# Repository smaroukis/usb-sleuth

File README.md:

See [this README](/README-downloading-firmware.md) for usage of the STM32CubeIDE to flash firmware on the device. 

## Overview

The device tests for continuity and internal resistors within various USB Cables and exposes some pins for multimeter testing. The project is a hardware fork of [aroerina/LimePulse](https://github.com/aroerina/LimePulse_USB_cable_checker/) that I decided to reverse engineer and write the firmware for.

A STM32C031K6T microcontroller is used for testing connection and orientation, powered by a CR2032 battery. Code is given using STM32 HAL libraries and the device can being programmed over SWD. 

KiCad and gerber files are provided for the board layout, as well as the library footprints for non-standard parts ordered from JLCPCB/LCSC. 
See the [BOM](/production/38-04-usb-tester_2023-12-18_rev1/bom.csv).

This USB cable tester has the "B" side on the right, and the "A" side on the left. Receptacles are given for the following:
- Type-C (both sides) 
- Type-C to A 
- Type-C to micro B (2.0)
- Type-C to mini B 

The device has some benefits over a simple continuity tester
- displays the as-plugged orientation of the 4 different possibilities of the USB-C to C cable
- detects pullup and pulldown resistors on the CC lines as required by the USB standard for legacy cables 
- identifies active cable with E marker (via the pulldown resistor present on VCONN)
- doesn't apply a +V to the Ground line/pin, instead it uses a MCU to test the presence of a connected ground wire
- exposes various pins to test cable and internal resistors manually with a DMM

## Example Tests

#### USB C-C Active Cable

> Note in this test only one of the USB 2.0 Data pair LEDs will light up depending on the cable orientation, showing that the two pairs are not connected inside the cable (the pairs are also not connected on the PCB). The user must flip the orientation to test both data pairs. 
#### DMM Test of Internal Resistor

Testing the value of the pulldown resistor on an active cable by measuring between `B_CC2` and `B_GND` (should be between 800-1.2K Ohms).

#### OTG Test

## General PCB Layout

Layout
- Various B side pins are biased to VBUS through pullup resistors. A side pins are either connected to ground through an LED, thus lighting up if the corresponding wire is continuous, or the pins are connected into the MCU for inputs. These pins that the MCU tests for are as follows:
- Ground (note all four GND pins are tied together)
- VBUS (note all four VBUS pins are tied together)
- CC1 to test for CC line and orientation
- CC2 to test for VCONN line and pull down resistor for active cables, as well as a flipped CC cable

> Note: Both A-side and B-side CC1 and CC2 pins are tapped off into corresponding control inputs to the MCU through a resistor, allowing for pulling the control pins high or low to sense the result on the opposite side.

Simplified layout of testing CC1 pin.

## Programming and Reset

Programming is done via the Serial Wire Debug headers (labeled `DEBUG`) via an STLink debugger probe. 

The device can also be reset by shorting out the `nRESET` line to `GND` (pins 1 and 2 on the header).

> [!CAUTION]
> In the case where the debugger is providing power to the target, make sure the `POWER` switch is `OFF`.

> [!NOTE]
> For the `SWD` pins we need pullup or pulldown resistors on `SWDIO` and `SDCLK` respectively. These are provided internally by the STM32 MCU, but if there is an issue with the debugger try adding an external weak pulllup and pulldown (10K-100K).

# Description of Operation

## Sensing VBUS and GND 

> [!NOTE]
> `VBUS`: Pulled up on B-side to VDD via 2K, pulled down to ground at A-side MCU input sense pin via 10K. Sense pin reads high if VBUS line is continuous through the cable.
> `GND`: B-side receptacle ground pin connected to board ground, A-side receptacle pin is direct to input sense pin.

All VBUS pins are tied together and tested via a pulldown resistor on the MCU (similarly for GND pins).

Most B-side receptacle pins are pulled up to supply/VDD through resistors with exception for CC pins and Ground. B-side ground is connected to board ground through a DIP switch for isolation from the MCU ground if needed.

A-side receptacle pins are connected to the MCU input for sensing.

`A_VBUS`/`A_GND` and connected to `VBUS_SENSE`/`GND_SENSE` inputs to the MCU through DIP switches for isolation from the MCU during DMM testing.

`VBUS_SENSE` pin is an input to the MCU with a pull down resistor forming a voltage divider with the 2K VDD pulllup resistor. If the `VBUS` line is discontinuous, the pin reads `LOW`. If `VBUS` is continuous then the pin reads `VCC`x10/12, or digital `HIGH`. 

Indicator LEDs are driven by the MCU outputs `GND_LED` and `VBUS_LED`.

# MCU Testing Logic

### Orientation of CC Pin

Here is the type-C receptacle pinout 

> Source: "USB 2.0 Type-C Plug Pin-Out" https://ww1.microchip.com/downloads/en/appnotes/00001953a.pdf

Possible orientations of USB-C Plug. 

> Note Ra is for the active pulldown emarker, but don't take this "straight through" configuration literally as there are diodes preventing shorting of the pins.

Simplified PCB layout:

We can determine that a C-C type cable is connected by pulling both A_CC1 and A_CC2 HIGH and CCx_CTRL pins LOW, then looking for one of the B_CCx pins coming HIGH.

### MCU Testing of Ra on Emarker (Active) Cables

The pulldown (Ra, for "active") is nominally 800-1.2K. Connection is as follows:

We simply configure the `A_CC2` and `B_CC2` pins as `INPUT_PULLUP`s and test if these lines (the `VCONN` line) are pulled low (normally it is open), since the pulldown Ra is strong at ~1K.

## MCU Testing of Rp on Type-A to Type-C Cable

> [!NOTE]
> It is programmed to work for both USB-C plug orientations

Setup
1. `VBUS` is connected to `VCC` through a 2K resistor (ignored for the calculations below)
2. Write `CC1_CTRL` and `CC2_CTRL` → `LOW` (pulls `B_CCx` pin toward ground through 10K R)
3. Perform analog read of `B_CC1_sense` and `B_CC2_SENSE`
4. If the analog read is above a threshold, `RP_THRESH`, to account for ground noise, then the 56K Rp pullup exists. 

> [!TIP]
> An analog read is required since the internal Rp is weak enough such that it doesn't pull it all the way up to the digital `HIGH` threshold

## MCU Testing of Rd on Type-B to Type-C Cable

> Note this works for both CC configurations

1. Set `A_CC1` as `INPUT_PULLUP` (~50K internal pullup)
2. Read `A_CC1`, if pulled `LOW`, then it means that `Rp` is present (Rd = 5K which is much stronger than the 50K internal pullup)

## Power Isolation For Testing

Isolation switches are provided to isolate the DMM from the MCU as it injects a test current to measure resistance, and also to allow us to measure the resistance of the cable itself (e.g. VBUS to GND). 

> Note during testing it was found that even with the switches closed the DMM measurements weren't affected.  

In the schematic these are modeled as a multi-unit DIP switch:
- `SW2A`: Separates `VCC` from `VBUS`
- `SW2B`: Separates `B_GND` from `GND`
- `SW2C`: Separates `A_GND` from `A_GND_SENSE` (input to MCU)
- `SW2D`: Separates `A_VBUS` from `A_VBUS_SENSE` (input to MCU)

# DMM Testing

## DMM Testing of  Rp on CC line

> [!Caution]
> Verify the following:
> 1. USB cable is in the normal CC Orientation of `STD>STD` before proceeding (or note the configuration to choose the correct pad to test)
> 2. All DIP switches are in the OFF position
> 3. Power switch is in the OFF position

For the Type-A to C cable the USB standard specifies at 56K pullup resistor between `VBUS` and `CC` (since the A side is the host, CC pin needs to be pulled up for the B-side/peripheral to recognize A side as host). 

We can test the exact value of this resistor by using a DMM between `B_VBUS` and `B_CC1` testing pads.

## DMM Testing of Rd

> [!Caution]
> Verify the following:
> 1. USB cable is in the normal CC Orientation of `STD>STD` before proceeding (or note the configuration to choose the correct pad to test)
> 2. All DIP switches are in the OFF position
> 3. Power switch is in the OFF position

For the Type-B to C cable the USB standard specifies at 5K6 pulldown resistor between `CC` and `GND` (since the B side is the peripheral, CC pin needs to be pulled down for the A-side/host to recognize B side as peripheral). 

We can test the exact value of this resistor by using a DMM between 
`A_GND` and `A_CC1` 

## DMM Testing of Ra

1. With device ON, make sure the CC orientation is `STD>STD`
2. Switch isolation switches to OFF
3. Switch power OFF
4. Place a DMM between `B_CC2` and `B_GND` since the Ra will be on the VCONN line.

# Shields and ID Pin

### Shields 
Shields are connected together and exposed to a through hole testing terminal. For this we can test with a multimeter. 

Note the shield and ground are connected inside the receptacle.

### ID (On The Go / OTG)

The OTG specification allows a USB device normally acting as a peripheral, to now act as a host (example use case: a tablet normally a peripheral, acting as a host can read from removable media on a flash drive)

For the OTG cable the A-plug side ties its ID pin to ground, and the B-plug side leaves it floating.  

Since the ID pin is supposed to be tied to its ground pin within the plug, we just connect an LED between VDD → ID pin (=Ground pin) to test the connection.

> The ID pin is also brought out on an exposed pad.

# FAQ

Only one set of the D+ and D- pins light up.
- The D1+/- and D2+/- pins are not connected together to allows the user to test both sets of pins independently (but requires the user to flip the USB-C side)

OTG Cable test doesn't work? 
- Make sure the test setup is as shown in the examples

> If the OTG cable has two male plugs, the data lines are not connected between the male ends, only from female → male 1 and female → male 2. The proper way to test will require the OTG adapter plus a normal USB cable. 

With one end plugged in, when I touch the other cable plug to the receptacle the GND (and sometimes Rd) LEDs light up.
- This happens because the tester first checks for VBUS=+Vsupply, and next checks for Ground=0V. If GND=0V it waits 300ms for the plug to "seat" before running through the other tests. But since the receptacle chassis and plug sheath are connected to GND, if you touch the plug to the receptacle it will read GND as 0V and proceed with the other tests. In the USB C<>B case, the Rd test will run if the CC pins aren't connected through on both sides, so it will also test once this contact is made.

# Notable Documentation

The USB-C Type Spec provides the Rp and Rd requirements for legacy cables.

For example, Type-C to 2.0 Type A:

USB Type-C Spec R2.3 - October 2023.pdf
> tl;dr any legacy cable assembly that **sources** power to a Type C connector must use the default 56K pullup (note this is for both 3.1 and 2.0 versions, since the power negotiation didn't come along until later)

Note the A5 CC pin and the B5 VCONN pin are **not** connected internally. This means it is up to the hardware developer to implement orientation detection on the C-receptacle side. 

And here is for the Type-C to 2.0 Micro-B:
 ^dzdzs5

# Improvements
- USB C<> Micro/Mini B D+/D- LED pair is dependent on C side orientation - make it more user friendly by only lighting up the bottom 2.0 row
- Low power

# Attributions
**Icons**
- Fedora Hat by Sanjib Biswas from [vecteezy](https://www.vecteezy.com/png/24758745-fedora-hat-transparent-background) -  <a href="https://www.vecteezy.com/free-png/silhouette">Silhouette PNGs by Vecteezy</a>
- tip by Hothouse Design from <a href="https://thenounproject.com/browse/icons/term/tip/" target="_blank" title="tip Icons">Noun Project</a> (CC BY 3.0)
- Warning by Deylotus Creative Design from <a href="https://thenounproject.com/browse/icons/term/warning/" target="_blank" title="Warning Icons">Noun Project</a> (CC BY 3.0)

**Inspired By**
- https://github.com/petl/USB-C-cable-tester-C2C-caberQU
- https://github.com/alvarop/usb_c_cable_tester
- https://github.com/aroerina/LimePulse_USB_cable_checker/ - original inspiration for the design and functionality from its professional quality layout

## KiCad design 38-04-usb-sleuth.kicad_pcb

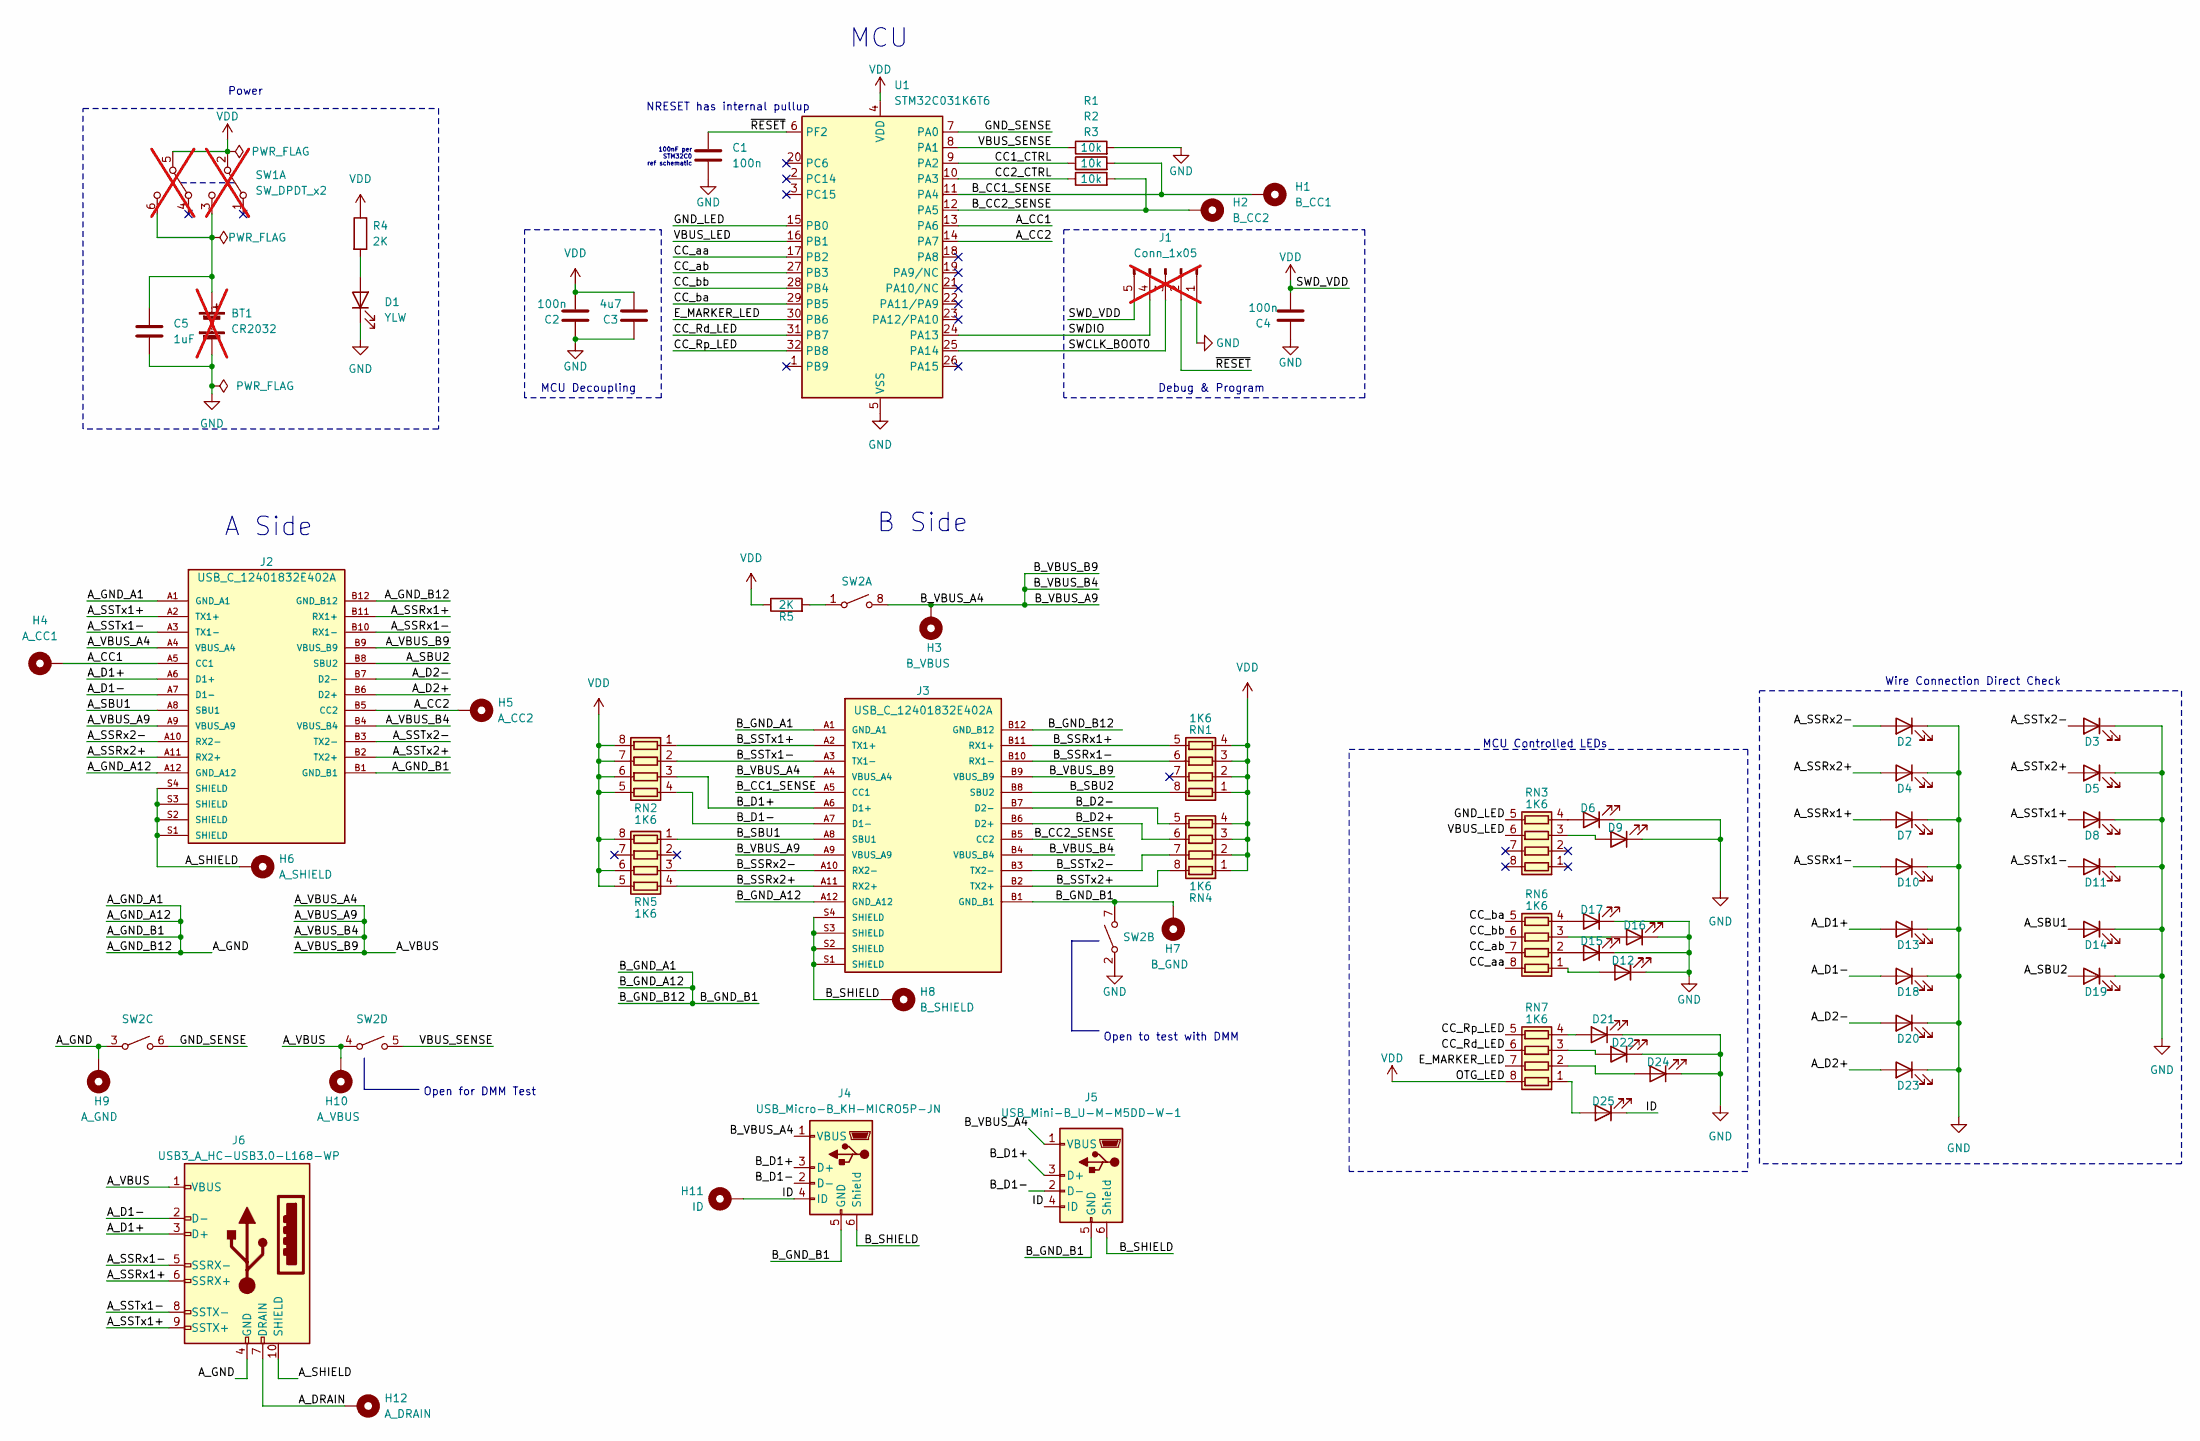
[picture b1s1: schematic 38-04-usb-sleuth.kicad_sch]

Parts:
BT1: CR2032; BatteryHolder_Keystone_103_1x20mm; LCSC Part # DNP; not fitted
C1, C2, C4: 100n; C_0402_1005Metric; LCSC Part # C1525
C3: 4u7; C_0805_2012Metric_Pad1.18x1.45mm_HandSolder; LCSC Part # C1779
C5: 1uF; C_0805_2012Metric_Pad1.18x1.45mm_HandSolder; LCSC Part # C28323
D1, D2, D3, D4, D5, D6, D7, D8, D9, D10, D11, D12, D13, D14, D15, D16, D17, D18, D19, D20, D21, D22, D23, D24, D25: YLW; LED_0805_2012Metric; LCSC Part # C2296
H1: B_CC1; Connector_Pad_Edge_Oval_5mm_Extended; LCSC Part # DNP
H2: B_CC2; Connector_Pad_Edge_Oval_5mm_Extended; LCSC Part # DNP
H3: B_VBUS; Connector_Pad_Edge_Oval_5mm_Extended; LCSC Part # DNP
H4: A_CC1; Connector_Pad_Edge_Oval_5mm_Extended; LCSC Part # DNP
H5: A_CC2; Connector_Pad_Edge_Oval_5mm_Extended; LCSC Part # DNP
H6: A_SHIELD; TestPoint_THTPad_D1.5mm_Drill0.7mm; LCSC Part # DNP
H7: B_GND; Connector_Pad_Edge_Oval_5mm_Extended; LCSC Part # DNP
H8: B_SHIELD; TestPoint_THTPad_D1.5mm_Drill0.7mm; LCSC Part # DNP
H9: A_GND; Connector_Pad_Edge_Oval_5mm_Extended; LCSC Part # DNP
H10: A_VBUS; Connector_Pad_Edge_Oval_5mm_Extended; LCSC Part # DNP
H11: ID; TestPoint_THTPad_D1.5mm_Drill0.7mm; LCSC Part # DNP
H12: A_DRAIN; TestPoint_THTPad_D1.5mm_Drill0.7mm; LCSC Part # DNP
J1: Conn_1x05; PinSocket_1x05_P2.54mm_Vertical; LCSC Part # DNP; not fitted
J2, J3: USB_C_12401832E402A; USB_C_Receptacle_Amphenol_12401832E402A; PARTREV X2; DigiKey_Part_Number 12401832E402ATR-ND
J4: USB_Micro-B_KH-MICRO5P-JN; USB_Micro-B_Kinghelm-KH-MICRO5P-JN; LCSC Part # C962222
J5: USB_Mini-B_U-M-M5DD-W-1; USB_Mini-B_Korean-Hroparts_U-M-M5DD-W-1_SMD-5-4MP; LCSC Part # C145778
J6: USB3_A_HC-USB3.0-L168-WP; USB3_A_Hong-Cheng_HC-USB3.0-L168-WP_THT-9-2MP_P2.0mm; LCSC Part # C7501850
R1, R2, R3: 10k; R_0805_2012Metric_Pad1.20x1.40mm_HandSolder; LCSC Part # C17414
R4, R5: 2K; R_0805_2012Metric_Pad1.20x1.40mm_HandSolder; LCSC Part # C17604
RN1, RN2, RN3, RN4, RN5, RN6, RN7: 1K6; R_Array_Concave_4x0402; LCSC Part # C728711
SW1: SW_DPDT_x2; SW_E-Switch_EG1271_SPDT; LCSC Part # DNP; not fitted
SW2: ZX-1.27BM-4PSMD; SW-DIP-4P_P1.27mm_SMD-2x4; LCSC Part # C5160896
U1: STM32C031K6T6; LQFP-32_7x7mm_P0.8mm; LCSC Part # C5456169

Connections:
/A_CC1: H4.1, J2.A5 (CC1), U1.13 (PA6)
/A_CC2: H5.1, J2.B5 (CC2), U1.14 (PA7)
/A_D1+: D13.2 (A), J2.A6 (D1+), J6.3 (D+)
/A_D1-: D18.2 (A), J2.A7 (D1-), J6.2 (D-)
/A_D2+: D23.2 (A), J2.B6 (D2+)
/A_D2-: D20.2 (A), J2.B7 (D2-)
/A_DRAIN: H12.1, J6.7 (DRAIN)
/A_GND: H9.1, J2.A1 (GND_A1), J2.A12 (GND_A12), J2.B1 (GND_B1), J2.B12 (GND_B12), J6.4 (GND), SW2.3
/A_GND_SENS: SW2.6, U1.7 (PA0)
/A_SBU1: D14.2 (A), J2.A8 (SBU1)
/A_SBU2: D19.2 (A), J2.B8 (SBU2)
/A_SHIELD: H6.1, J2.S1 (SHIELD), J2.S2 (SHIELD), J2.S3 (SHIELD), J2.S4 (SHIELD), J6.10 (SHIELD)
/A_SSRx1+: D7.2 (A), J2.B11 (RX1+), J6.6 (SSRX+)
/A_SSRx1-: D10.2 (A), J2.B10 (RX1-), J6.5 (SSRX-)
/A_SSRx2+: D4.2 (A), J2.A11 (RX2+)
/A_SSRx2-: D2.2 (A), J2.A10 (RX2-)
/A_SSTx1+: D8.2 (A), J2.A2 (TX1+), J6.9 (SSTX+)
/A_SSTx1-: D11.2 (A), J2.A3 (TX1-), J6.8 (SSTX-)
/A_SSTx2+: D5.2 (A), J2.B2 (TX2+)
/A_SSTx2-: D3.2 (A), J2.B3 (TX2-)
/A_VBUS: H10.1, J2.A4 (VBUS_A4), J2.A9 (VBUS_A9), J2.B4 (VBUS_B4), J2.B9 (VBUS_B9), J6.1 (VBUS), SW2.4
/A_VBUS_SENS: R1.1, SW2.5, U1.8 (PA1)
/B_CC1_SENS: H1.1, J3.A5 (CC1), R2.2, U1.11 (PA4)
/B_CC2_SENS: H2.1, J3.B5 (CC2), R3.2, U1.12 (PA5)
/B_D1+: J3.A6 (D1+), J4.3 (D+), J5.3 (D+), RN2.3 (R3.1)
/B_D1-: J3.A7 (D1-), J4.2 (D-), J5.2 (D-), RN2.4 (R4.1)
/B_D2+: J3.B6 (D2+), RN4.6 (R3.2)
/B_D2-: J3.B7 (D2-), RN4.5 (R4.2)
/B_GND_A1: H7.1, J3.A1 (GND_A1), J3.A12 (GND_A12), J3.B1 (GND_B1), J3.B12 (GND_B12), J4.5 (GND), J5.5 (GND), SW2.7
/B_SBU1: J3.A8 (SBU1), RN5.1 (R1.1)
/B_SBU2: J3.B8 (SBU2), RN1.8 (R1.2)
/B_SHIELD: H8.1, J3.S1 (SHIELD), J3.S2 (SHIELD), J3.S3 (SHIELD), J3.S4 (SHIELD), J4.6 (Shield), J5.6 (Shield)
/B_SSRx1+: J3.B11 (RX1+), RN1.5 (R4.2)
/B_SSRx1-: J3.B10 (RX1-), RN1.6 (R3.2)
/B_SSRx2+: J3.A11 (RX2+), RN5.4 (R4.1)
/B_SSRx2-: J3.A10 (RX2-), RN5.3 (R3.1)
/B_SSTx1+: J3.A2 (TX1+), RN2.1 (R1.1)
/B_SSTx1-: J3.A3 (TX1-), RN2.2 (R2.1)
/B_SSTx2+: J3.B2 (TX2+), RN4.8 (R1.2)
/B_SSTx2-: J3.B3 (TX2-), RN4.7 (R2.2)
/B_VBUS_A4: H3.1, J3.A4 (VBUS_A4), J3.A9 (VBUS_A9), J3.B4 (VBUS_B4), J3.B9 (VBUS_B9), J4.1 (VBUS), J5.1 (VBUS), SW2.8
/CC1_CTRL: R2.1, U1.9 (PA2)
/CC2_CTRL: R3.1, U1.10 (PA3)
/CC_Rd_LED: RN7.6 (R3.2), U1.31 (PB7)
/CC_Rp_LED: RN7.5 (R4.2), U1.32 (PB8)
/CC_aa: RN6.8 (R1.2), U1.17 (PB2)
/CC_ab: RN6.7 (R2.2), U1.27 (PB3)
/CC_ba: RN6.5 (R4.2), U1.29 (PB5)
/CC_bb: RN6.6 (R3.2), U1.28 (PB4)
/E_MARKER_LED: RN7.7 (R2.2), U1.30 (PB6)
/GND_LED: RN3.5 (R4.2), U1.15 (PB0)
/ID: D25.1 (K), H11.1, J4.4 (ID), J5.4 (ID)
/SWCLK_BOOT0: J1.3, U1.25 (PA14)
/SWDIO: J1.4, U1.24 (PA13)
/VBUS_LED: RN3.6 (R3.2), U1.16 (PB1)
/~RESET: C1.1, J1.2, U1.6 (PF2)
GND: BT1.2 (-), C1.2, C2.1, C3.1, C4.1, C5.2, D1.1 (K), D2.1 (K), D3.1 (K), D4.1 (K), D5.1 (K), D6.1 (K), D7.1 (K), D8.1 (K), D9.1 (K), D10.1 (K), D11.1 (K), D12.1 (K), D13.1 (K), D14.1 (K), D15.1 (K), D16.1 (K), D17.1 (K), D18.1 (K), D19.1 (K), D20.1 (K), D21.1 (K), D22.1 (K), D23.1 (K), D24.1 (K), J1.1, R1.2, SW2.2, U1.5 (VSS)
unnamed: BT1.1 (+), C5.1, SW1.3 (C), SW1.6 (C)
unnamed: D1.2 (A), R4.2
unnamed: D6.2 (A), RN3.4 (R4.1)
unnamed: D9.2 (A), RN3.3 (R3.1)
unnamed: D12.2 (A), RN6.1 (R1.1)
unnamed: D15.2 (A), RN6.2 (R2.1)
unnamed: D16.2 (A), RN6.3 (R3.1)
unnamed: D17.2 (A), RN6.4 (R4.1)
unnamed: D21.2 (A), RN7.4 (R4.1)
unnamed: D22.2 (A), RN7.3 (R3.1)
unnamed: D24.2 (A), RN7.2 (R2.1)
unnamed: D25.2 (A), RN7.1 (R1.1)
unnamed: R5.2, SW2.1
VCC: C2.2, C3.2, C4.2, J1.5, R4.1, R5.1, RN1.1 (R1.1), RN1.2 (R2.1), RN1.3 (R3.1), RN1.4 (R4.1), RN2.5 (R4.2), RN2.6 (R3.2), RN2.7 (R2.2), RN2.8 (R1.2), RN4.1 (R1.1), RN4.2 (R2.1), RN4.3 (R3.1), RN4.4 (R4.1), RN5.5 (R4.2), RN5.6 (R3.2), RN5.8 (R1.2), RN7.8 (R1.2), SW1.2 (B), SW1.5 (B), U1.4 (VDD)

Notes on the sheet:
MCU Controlled LEDs
Wire Connection Direct Check
MCU
100nF per STM32C0 ref schematic
NRESET has internal pullup
Power
Debug & Program
Open to test with DMM
A Side
Open for DMM Test
B Side
MCU Decoupling

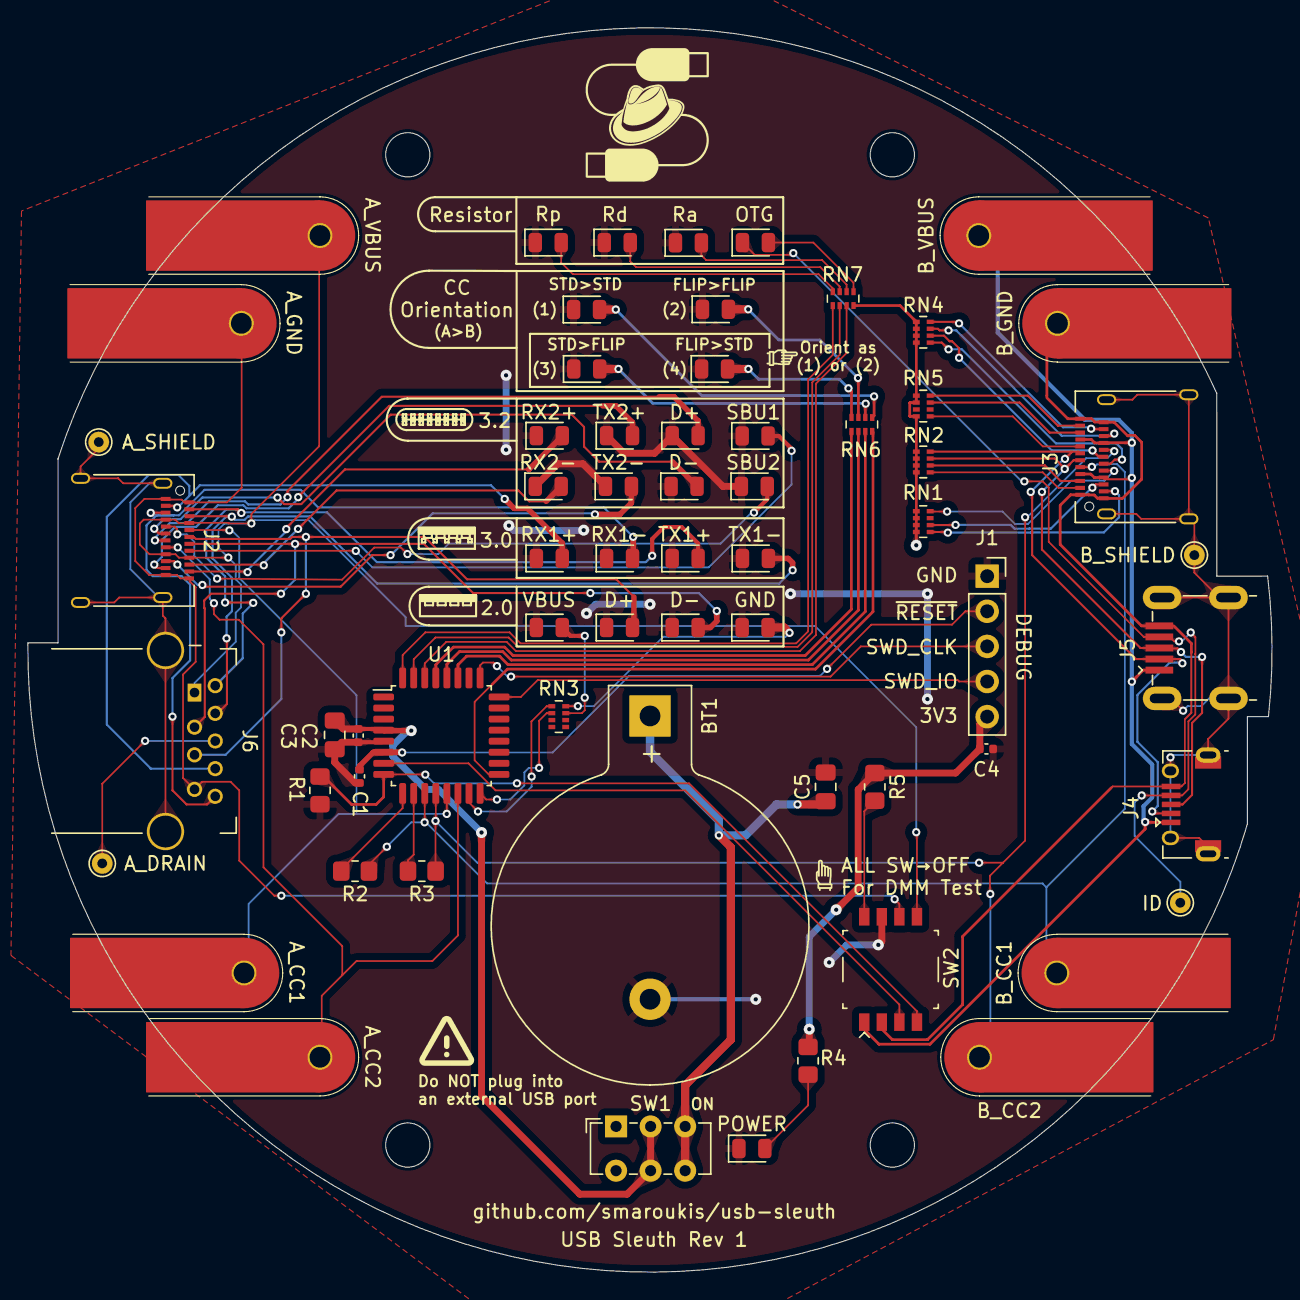
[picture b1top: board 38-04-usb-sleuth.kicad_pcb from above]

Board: 2 copper layers, 90.0 x 90.0 mm, 64 parts (0 on the bottom side), 71 nets.

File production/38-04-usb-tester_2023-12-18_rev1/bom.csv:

Designator,Footprint,Quantity,Value,LCSC Part #
"C1, C2, C4",402,3,100n,C1525
C3,805,1,4u7,C1779
C5,805,1,1uF,C28323
"D1, D10, D11, D12, D13, D14, D15, D16, D17, D18, D19, D2, D20, D21, D22, D23, D24, D25, D3, D4, D5, D6, D7, D8, D9",805,25,YLW,C2296
"J2, J3",USB_C_Receptacle_Amphenol_12401832E402A,2,USB_C_12401832E402A,C464604
J4,USB_Micro-B_Kinghelm-KH-MICRO5P-JN,1,USB_Micro-B_KH-MICRO5P-JN,C962222
J5,USB_Mini-B_Korean-Hroparts_U-M-M5DD-W-1_SMD-5-4MP,1,USB_Mini-B_U-M-M5DD-W-1,C145778
J6,USB3_A_Hong-Cheng_HC-USB3.0-L168-WP_THT-9-2MP_P2.0mm,1,USB3_A_HC-USB3.0-L168-WP,C7501850
"R1, R2, R3",805,3,10k,C17414
"R4, R5",805,2,2K,C17604
"RN1, RN2, RN3, RN4, RN5, RN6, RN7",R_Array_Concave_4x0402,7,1K6,C728711
SW2,SW-DIP-4P_P1.27mm_SMD-2x4,1,ZX-1.27BM-4PSMD,C5160896
U1,LQFP-32_7x7mm_P0.8mm,1,STM32C031K6T6,C5456169

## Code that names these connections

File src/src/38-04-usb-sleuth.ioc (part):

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Mcu.Name=STM32C031K(4-6)Tx
Mcu.Package=LQFP32
Mcu.UserName=STM32C031K6Tx
PA0.GPIOParameters=GPIO_Label
PA0.GPIO_Label=GND_SENSE
PA0.Signal=GPIO_Input
PA1.GPIOParameters=GPIO_Label
PA1.GPIO_Label=VBUS_SENSE
PA1.Signal=GPIO_Input
PA13.Mode=Serial_Wire
PA13.Signal=DEBUG_SWDIO
PA14-BOOT0.Mode=Serial_Wire
PA14-BOOT0.Signal=DEBUG_SWCLK
PA2.GPIOParameters=GPIO_Label
PA2.GPIO_Label=CC1_CTRL
PA2.Signal=GPIO_Output
PA3.GPIOParameters=GPIO_Label
PA3.GPIO_Label=CC2_CTRL
PA3.Signal=GPIO_Output
PA4.GPIOParameters=GPIO_Label
PA4.GPIO_Label=B_CC1_SENSE
PA4.Mode=IN4
PA4.Signal=ADC1_IN4
PA5.GPIOParameters=GPIO_Label
PA5.GPIO_Label=B_CC2_SENSE
PA5.Signal=ADC1_IN5
PA6.GPIOParameters=GPIO_Label
PA6.GPIO_Label=A_CC1
PA6.Signal=ADC1_IN6
PA7.GPIOParameters=GPIO_Label
PA7.GPIO_Label=A_CC2
PA7.Signal=ADC1_IN7
PA8.Signal=S_TIM1_CH1
PB0.GPIOParameters=GPIO_Label
PB0.GPIO_Label=GND_LED
PB0.Signal=GPIO_Output
PB1.GPIOParameters=GPIO_Label
PB1.GPIO_Label=VBUS_LED
PB1.Signal=GPIO_Output
PB2.GPIOParameters=GPIO_Label
PB2.GPIO_Label=CC_aa
PB2.Signal=GPIO_Output
PB3.GPIOParameters=GPIO_Label
PB3.GPIO_Label=CC_ab
PB3.Signal=GPIO_Output
PB4.GPIOParameters=GPIO_Label
PB4.GPIO_Label=CC_bb
PB4.Signal=GPIO_Output
PB5.GPIOParameters=GPIO_Label
PB5.GPIO_Label=CC_ba
PB5.Signal=GPIO_Output
PB6.GPIOParameters=GPIO_Label
PB6.GPIO_Label=E_MARKER_LED
PB6.Signal=GPIO_Output
PB7.GPIOParameters=GPIO_Label
PB7.GPIO_Label=CC_Rd_LED
PB7.Signal=GPIO_Output
PB8.GPIOParameters=GPIO_Label
PB8.GPIO_Label=CC_Rp_LED
PB8.Signal=GPIO_Output
RCC.HSE_VALUE=8000000
RCC.SYSCLKFreq_VALUE=48000000
board=custom

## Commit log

2023-11-15 first design
2023-11-16 changed to usb port 24 pins
2023-11-16 direct led connections
2023-11-21 STM32 layout
2023-11-22 added through holes for testing and vbus-sense resistor
2023-11-27 code - gnd and vbus testing
2023-11-27 tested hardware through Rd pulldown
2023-12-05 added new footprints, schematic edits
2023-12-06 mini b and dip switch footprint and schems
2023-12-07 edge pads and start of pcb layout
2023-12-08 pcb layout - cleanup, DNP decisions
2023-12-08 pre commit to importing template
2023-12-08 added defaults for jlpcb, fixed usb schematics
2023-12-11 started routing
2023-12-11 layout of LHS usb
2023-12-11 routing LEDs, started USB B side
2023-12-12 via size change refactoring DRC errors
2023-12-12 more layout DRC fixes
2023-12-12 more layouts and DRC routing
2023-12-12 board layouts and edge cut edits
2023-12-13 moved usb footprints from board edge
2023-12-14 renamed user symbol file
2023-12-14 renamed libraries
2023-12-14 added readme
2023-12-14 added screenshot
2023-12-14 attributions
2023-12-14 added schematic
2023-12-15 edited schematic, added solder mask expansion, added more thermal reliefs
2023-12-18 rev 1 sent for prod
2023-12-18 cleanup docs and assets for rev1
2023-12-19 correct SW2 footprint and symbol pin numbering
2024-01-17 manufcatured rev 1
2024-01-17 project name changes
2024-01-24 touch main.c
2024-01-25 cc STD>STD orientation OK
2024-01-25 cc orientation and Ra TESTED
2024-01-26 ADC first pass for Rp - works but not great
2024-01-26 adc continuous with user channel select functions
2024-01-26 ADC single shot single channel - for testing Rp flip/std
2024-01-27 changed VBUS/GND sense test order to start fixing Rp/Rd testing bug for C<>C cable
2024-01-27 fixed active Ra tests
2024-01-27 fixed CC orientation for all 4 cases
2024-01-27 active cable and cc configuration working together
2024-01-27 fixed Rd testing issue for C<>B
2024-01-29 readme updates
2024-01-31 cleanup file structure and add cubeIDE files
2024-01-31 added license
2024-01-31 updated license
2024-04-27 adding stm32ide project files and HAL Drivers
2024-04-27 firmware how-to readme
